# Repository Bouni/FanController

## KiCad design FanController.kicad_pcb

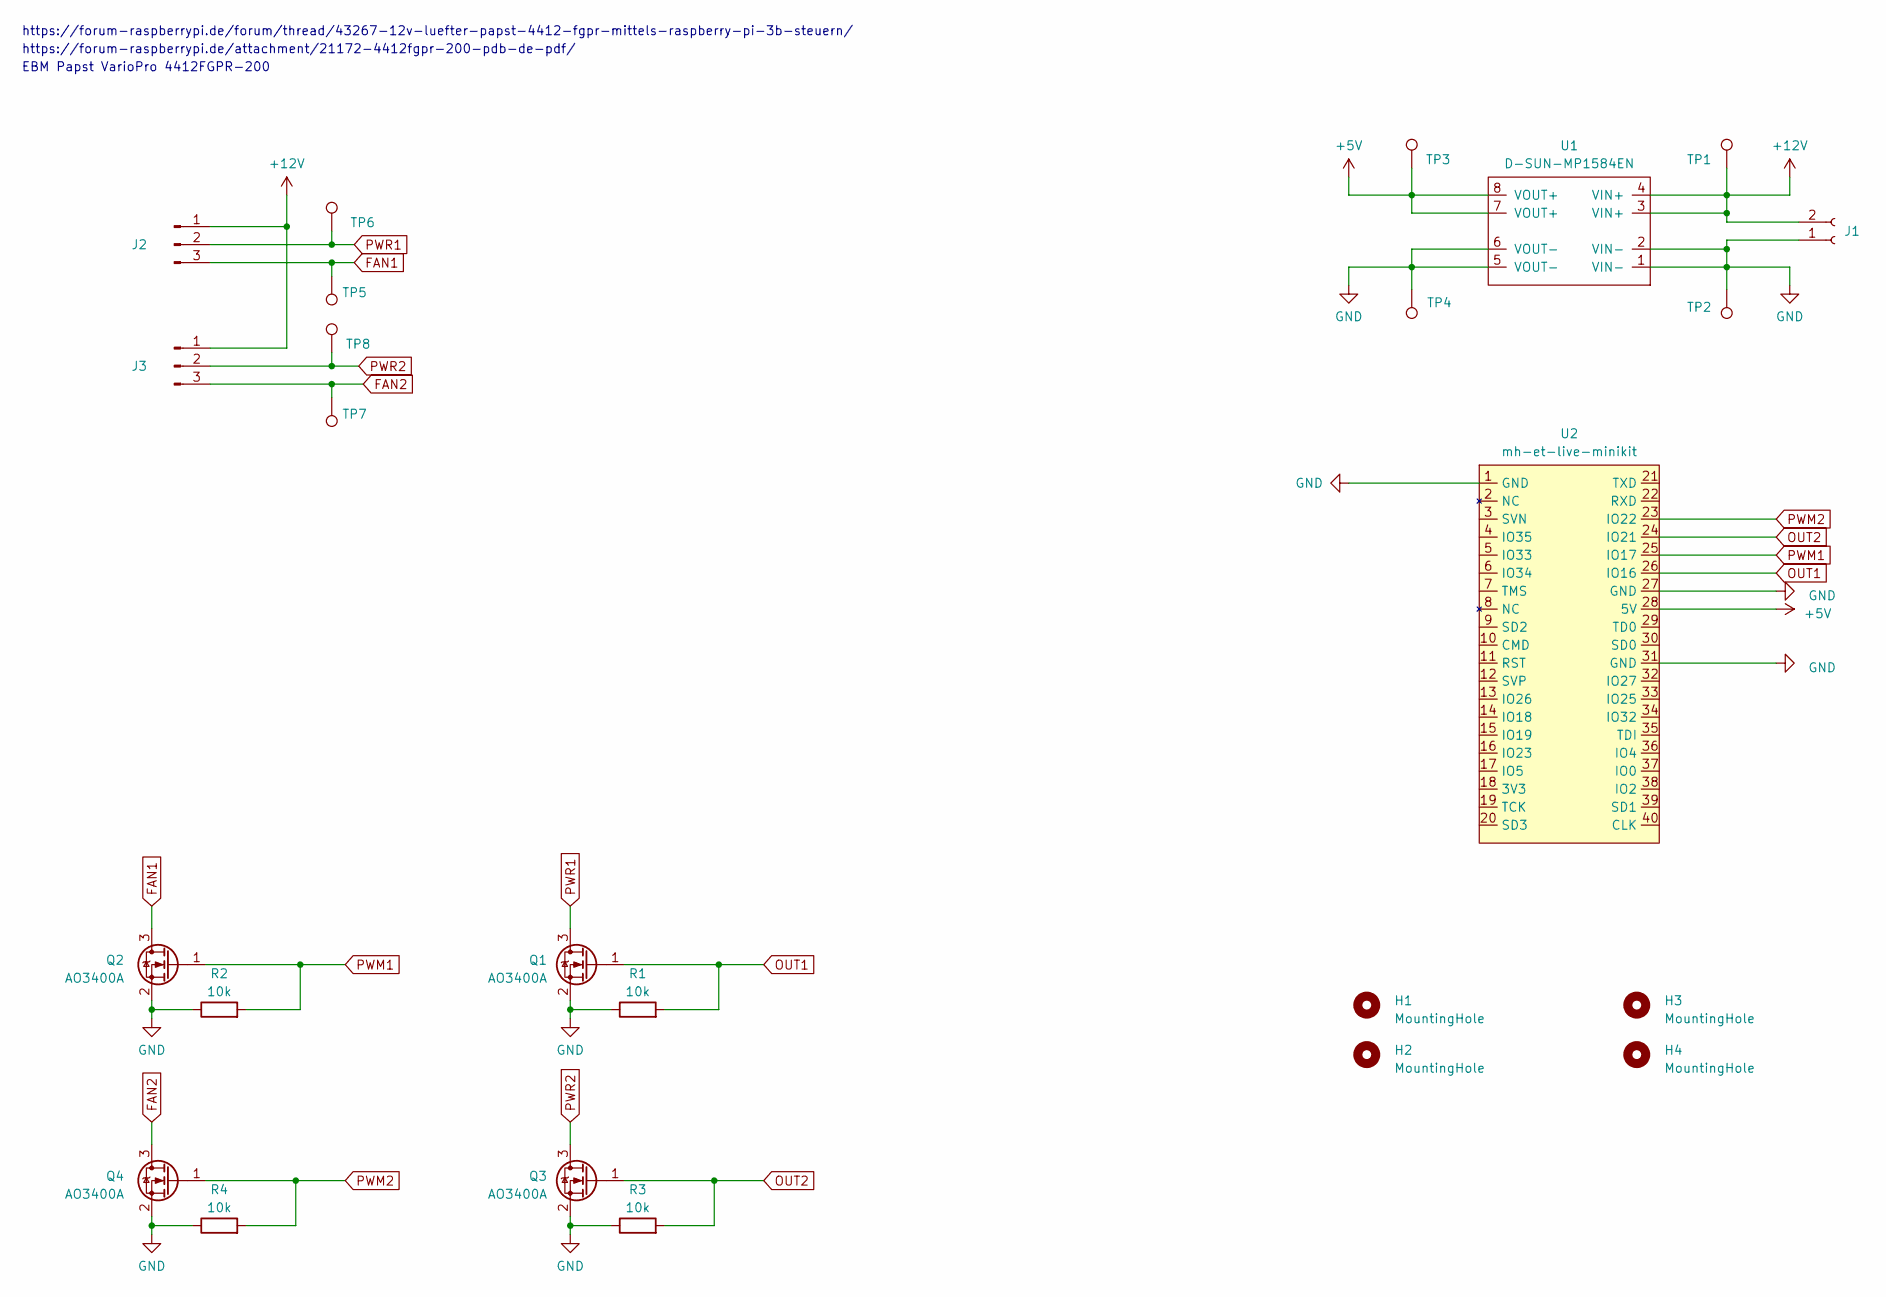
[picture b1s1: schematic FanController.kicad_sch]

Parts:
H1, H2, H3, H4: MountingHole; MountingHole_3.2mm_M3_DIN965
J1: Conn_01x02_Female; TerminalBlock_Phoenix_MKDS-1,5-2-5.08_1x02_P5.08mm_Horizont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
J2, J3: Conn_01x03_Male; TerminalBlock_Phoenix_MKDS-1,5-3-5.08_1x03_P5.08mm_Horizont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
Q1, Q2, Q3, Q4: AO3400A; SOT-23
R1, R2, R3, R4: 10k; R_0805_2012Metric_Pad1.20x1.40mm_HandSolder
TP1, TP2, TP3, TP4, TP5, TP6, TP7, TP8: TestPoint; TestPoint_Pad_D2.0mm
U1: D-SUN-MP1584EN
U2: mh-et-live-minikit; MH-ET LIVE MiniKit

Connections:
+5V: TP3.1, U1.7 (VOUT+), U1.8 (VOUT+), U2.28 (5V)
+12V: J1.2, J2.1, J3.1, TP1.1, U1.3 (VIN+), U1.4 (VIN+)
FAN1: J2.3, Q2.3 (D), TP5.1
FAN2: J3.3, Q4.3 (D), TP7.1
GND: J1.1, Q1.2 (S), Q2.2 (S), Q3.2 (S), Q4.2 (S), R1.1, R2.1, R3.1, R4.1, TP2.1, TP4.1, U1.1 (VIN-), U1.2 (VIN-), U1.5 (VOUT-), U1.6 (VOUT-), U2.1 (GND), U2.27 (GND), U2.31 (GND)
OUT1: Q1.1 (G), R1.2, U2.26 (IO16)
OUT2: Q3.1 (G), R3.2, U2.24 (IO21)
PWM1: Q2.1 (G), R2.2, U2.25 (IO17)
PWM2: Q4.1 (G), R4.2, U2.23 (IO22)
PWR1: J2.2, Q1.3 (D), TP6.1
PWR2: J3.2, Q3.3 (D), TP8.1

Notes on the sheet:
https://forum-raspberrypi.de/forum/thread/43267-12v-luefter-papst-4412-fgpr-mittels-raspberry-pi-3b-steuern/
https://forum-raspberrypi.de/attachment/21172-4412fgpr-200-pdb-de-pdf/
EBM Papst VarioPro 4412FGPR-200

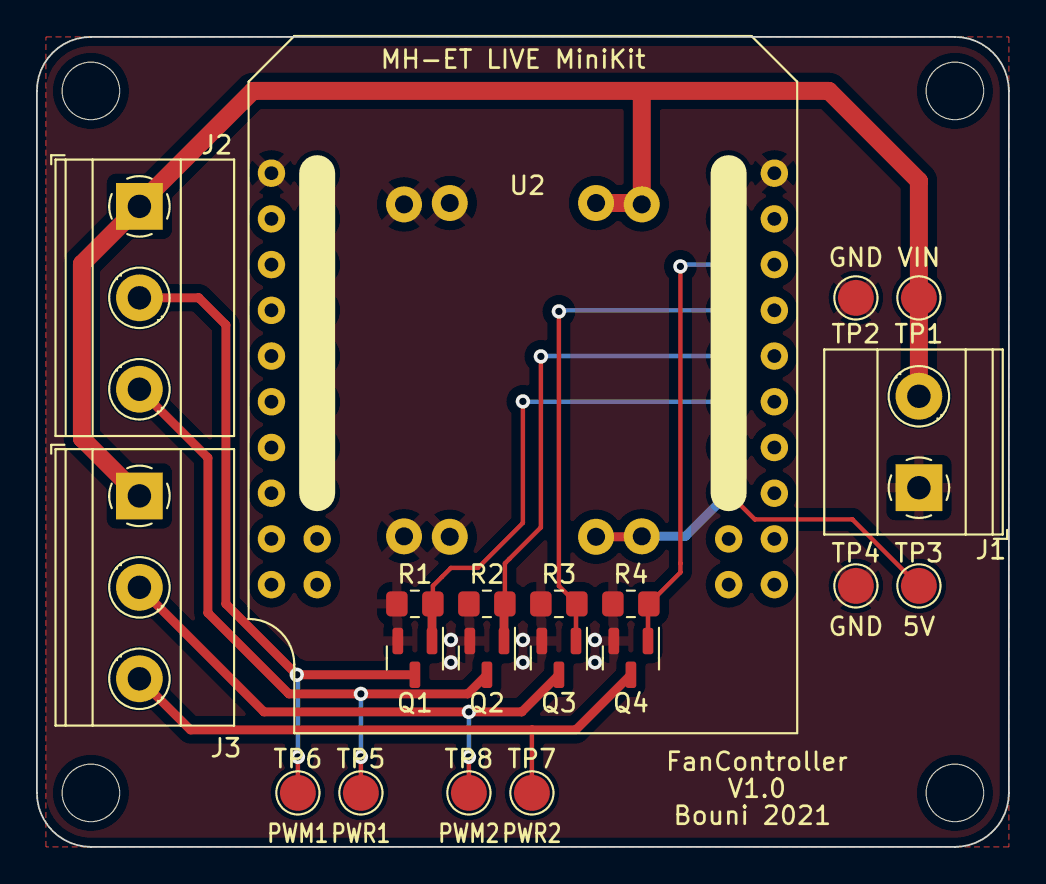
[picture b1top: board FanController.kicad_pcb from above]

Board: 2 copper layers, 54.0 x 45.0 mm, 25 parts (1 on the bottom side), 11 nets.

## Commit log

2021-07-05 shrinked board
2021-07-05 add BOM + CPL for JLCPCB
2021-07-22 add esphome based firmware config
2021-10-05 minor cleanups
2021-10-10 add captive portal for wifi config
2021-10-10 add exmples secretes.yaml
